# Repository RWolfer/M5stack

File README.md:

# M5stack
M5Stack PCB-Layouts, EAGLE-library and Information

#Board "Atomic":
https://docs.m5stack.com/#/en/atom/atomic
PCB-File: https://github.com/m5stack/M5-3D_and_PCB/blob/master/Atomic_V1.0.PcbDoc

#Board "Atom Hub Proto"
https://docs.m5stack.com/#/en/atom/atomhub
PCB-File: https://github.com/m5stack/m5-structural-design-file/blob/master/PCB/AtomHubProto.PcbDoc

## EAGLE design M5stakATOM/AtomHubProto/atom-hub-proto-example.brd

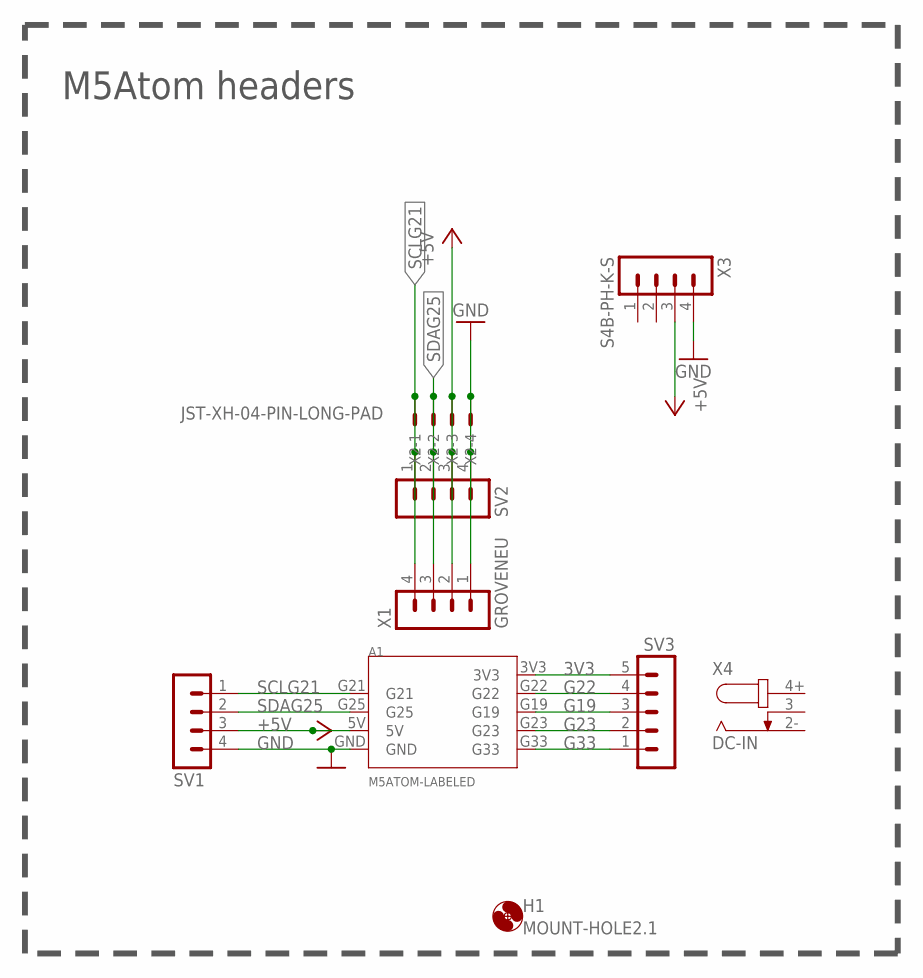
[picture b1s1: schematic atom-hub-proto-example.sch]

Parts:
A1: M5ATOM-LABELED; M5ATOM-W/-LABELS
H1: MOUNT-HOLE2.1; 2,1
SV1, SV2: MA04-1
SV3: MA05-1
X1: GROVENEU; GROVE-NEU
X2: JST-XH-04-PIN-LONG-PAD; JST-XH-04-PACKAGE-LONG-PAD
X3: S4B-PH-K-S
X4: DC-IN; DC-IN-TH_DC-0440-2.5A-2.0

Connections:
3V3: A1.3V3, SV3.5
+5V: A1.5V, SV1.3, SV2.3, X1.2, X2.3, X3.3
G19: A1.G19, SV3.3
G22: A1.G22, SV3.4
G23: A1.G23, SV3.2
G33: A1.G33, SV3.1
GND: A1.GND, SV1.4, SV2.4, X1.1, X2.4, X3.4
SCLG21: A1.G21, SV1.1, SV2.1, X1.4, X2.1
SDAG25: A1.G25, SV1.2, SV2.2, X1.3, X2.2

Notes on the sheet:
M5Atom headers

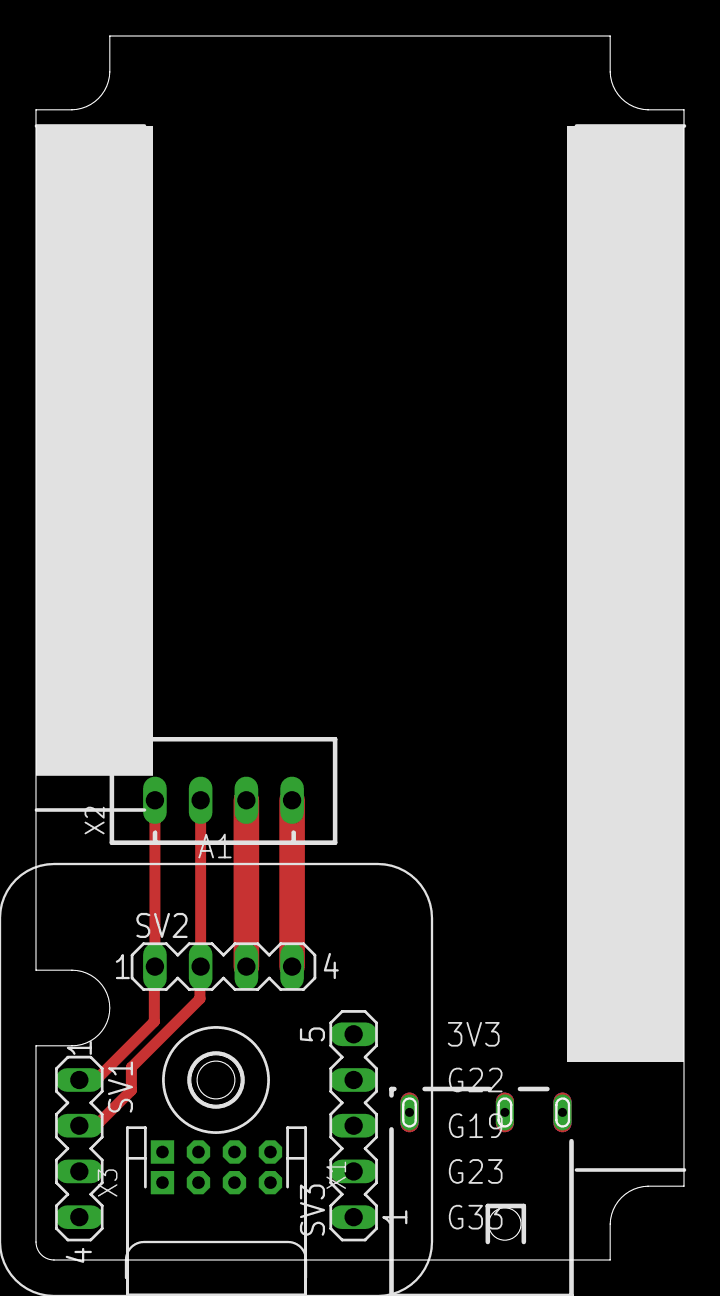
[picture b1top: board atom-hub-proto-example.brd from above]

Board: 2 copper layers, 36.0 x 68.0 mm, 9 parts (0 on the bottom side), 9 nets.

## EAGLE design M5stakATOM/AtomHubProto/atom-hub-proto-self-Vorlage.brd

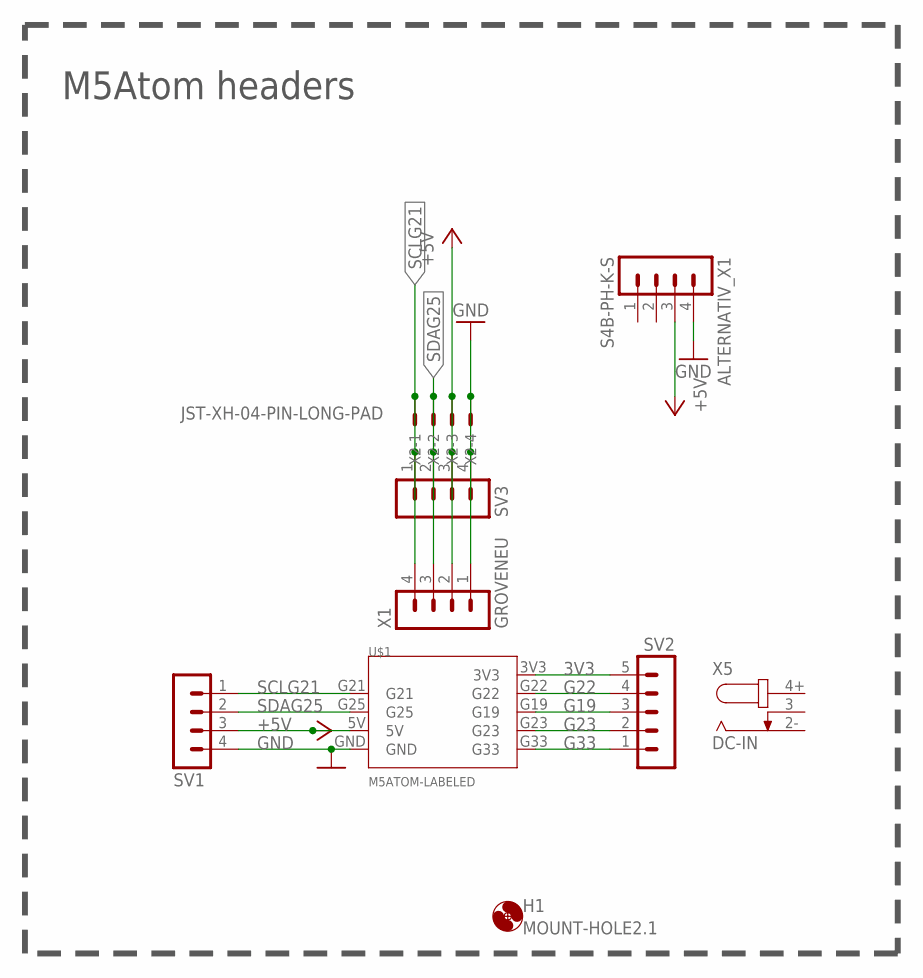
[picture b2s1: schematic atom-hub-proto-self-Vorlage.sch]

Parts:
ALTERNATIV_X1: S4B-PH-K-S
H1: MOUNT-HOLE2.1; 2,1
SV1, SV3: MA04-1
SV2: MA05-1
U$1: M5ATOM-LABELED; M5ATOM-W/-LABELS
X1: GROVENEU; GROVE-NEU
X2: JST-XH-04-PIN-LONG-PAD; JST-XH-04-PACKAGE-LONG-PAD
X5: DC-IN; DC-IN-TH_DC-0440-2.5A-2.0

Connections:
3V3: SV2.5, U$1.3V3
+5V: ALTERNATIV_X1.3, SV1.3, SV3.3, U$1.5V, X1.2, X2.3
G19: SV2.3, U$1.G19
G22: SV2.4, U$1.G22
G23: SV2.2, U$1.G23
G33: SV2.1, U$1.G33
GND: ALTERNATIV_X1.4, SV1.4, SV3.4, U$1.GND, X1.1, X2.4
SCLG21: SV1.1, SV3.1, U$1.G21, X1.4, X2.1
SDAG25: SV1.2, SV3.2, U$1.G25, X1.3, X2.2

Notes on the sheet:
M5Atom headers

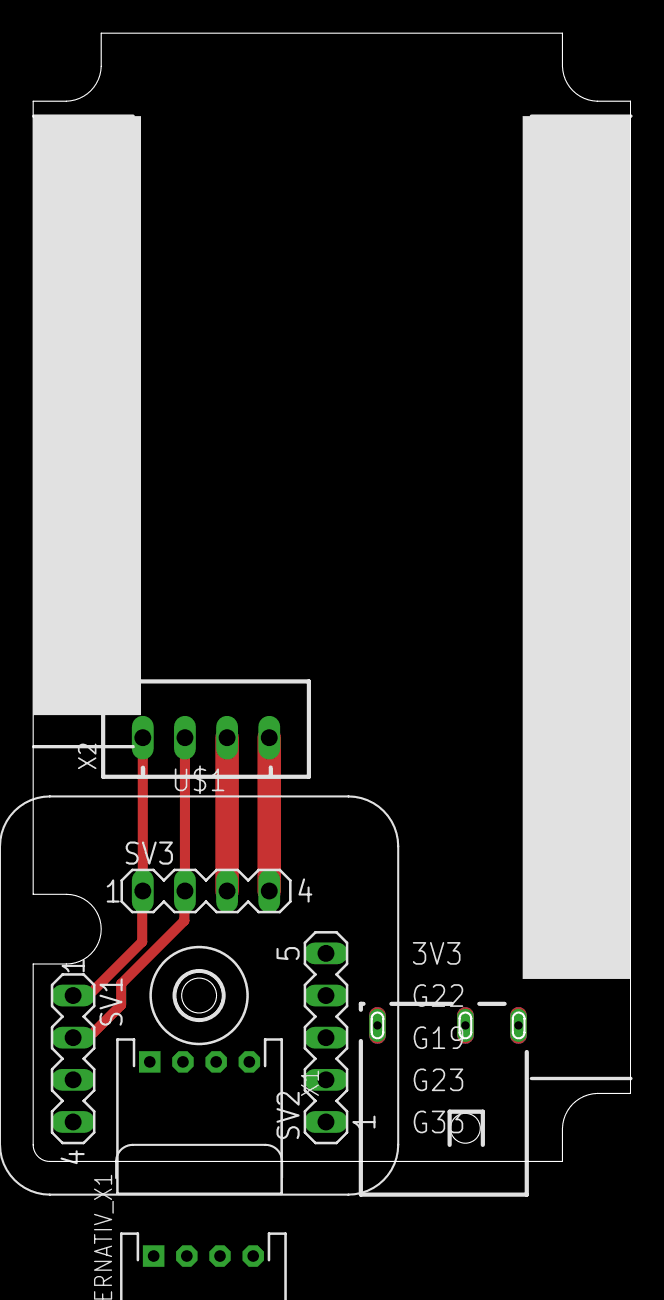
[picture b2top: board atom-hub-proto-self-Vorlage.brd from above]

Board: 2 copper layers, 36.0 x 68.0 mm, 9 parts (0 on the bottom side), 9 nets.

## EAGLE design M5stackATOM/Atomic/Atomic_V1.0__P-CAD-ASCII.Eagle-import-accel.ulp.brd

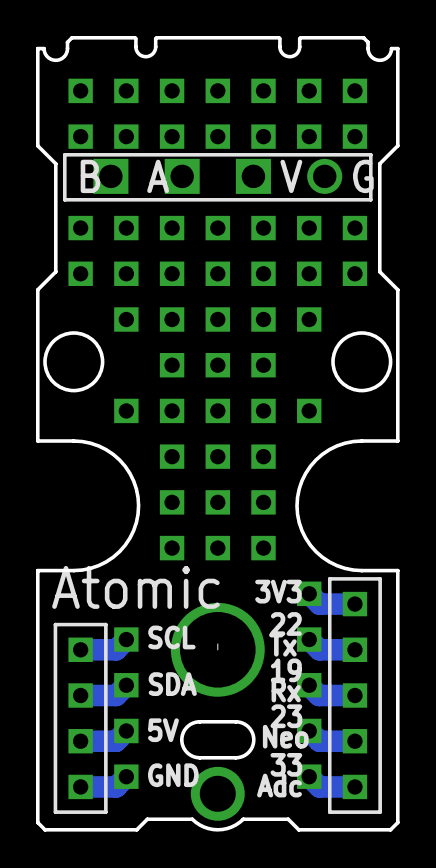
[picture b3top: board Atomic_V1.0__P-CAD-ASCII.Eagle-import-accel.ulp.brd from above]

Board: 2 copper layers, 20.0 x 44.0 mm, 76 parts (0 on the bottom side), 8 nets.

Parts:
DUMMY1: P:EX165Y165D1651
DUMMY2, DUMMY3, DUMMY4, DUMMY5, DUMMY6, DUMMY7, DUMMY8, DUMMY9, DUMMY10, DUMMY21, DUMMY22, DUMMY23, DUMMY24, DUMMY25, DUMMY26, DUMMY27, DUMMY28, DUMMY29, DUMMY30, DUMMY31, DUMMY32, DUMMY33, DUMMY34, DUMMY35, DUMMY36, DUMMY37, DUMMY38, DUMMY39, DUMMY40, DUMMY41, DUMMY42, DUMMY43, DUMMY44, DUMMY45, DUMMY46, DUMMY47, DUMMY48, DUMMY49, DUMMY50, DUMMY51, DUMMY52, DUMMY53, DUMMY54, DUMMY55, DUMMY56, DUMMY57, DUMMY58, DUMMY59, DUMMY60, DUMMY61, DUMMY62, DUMMY63, DUMMY64, DUMMY65, DUMMY66, DUMMY71, DUMMY72, DUMMY73, DUMMY74: P:RRX55Y55D331
DUMMY11: P:EX79Y79D791
DUMMY12, DUMMY13, DUMMY14, DUMMY15, DUMMY16, DUMMY17, DUMMY18, DUMMY20: P:RRX47Y47D331
DUMMY19: P:SX47Y47D331
DUMMY67: P:EX71Y71D511
DUMMY68, DUMMY69: P:RRX71Y71D511
DUMMY70: P:SX71Y71D511
DUMMY75: EF154X154MID1
DUMMY76: EF154X154MID2

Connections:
S$1: DUMMY10.P$1, DUMMY18.P$1
S$2: DUMMY9.P$1, DUMMY17.P$1
S$4: DUMMY5.P$1, DUMMY15.P$1
S$5: DUMMY3.P$1, DUMMY14.P$1
S$6: DUMMY8.P$1, DUMMY12.P$1
S$7: DUMMY6.P$1, DUMMY13.P$1
S$8: DUMMY4.P$1, DUMMY19.P$1
S$9: DUMMY2.P$1, DUMMY20.P$1

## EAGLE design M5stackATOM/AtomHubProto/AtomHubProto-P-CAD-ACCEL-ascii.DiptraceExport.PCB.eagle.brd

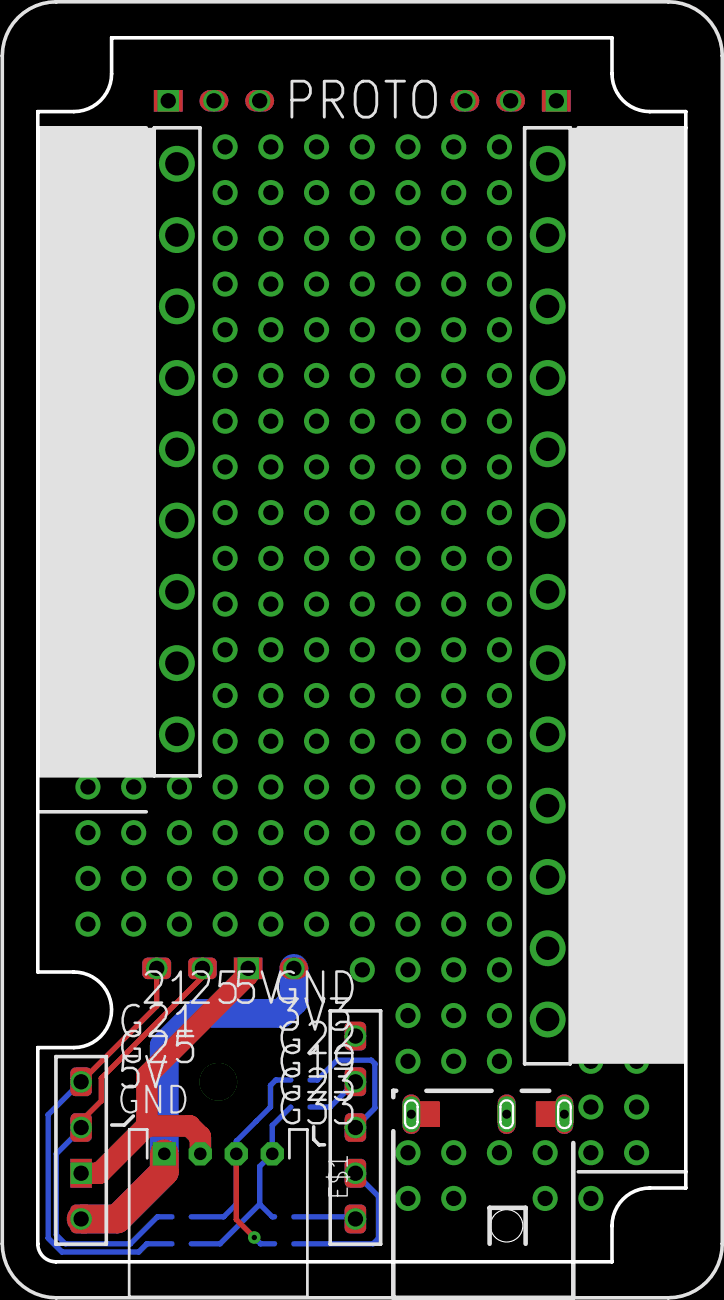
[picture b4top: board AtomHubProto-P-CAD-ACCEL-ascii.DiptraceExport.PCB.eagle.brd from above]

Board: 2 copper layers, 36.0 x 68.0 mm, 304 parts (0 on the bottom side), 4 nets.

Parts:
DC-IN-TH_DC-0440-2.5A-2.0: XKB Connectivity DC-0440-2.5A-2.0; DC-IN-TH_DC-0440-2.5A-2.0
E$1: GROVE-NEU
FREEPAD0, FREEPAD1, FREEPAD2, FREEPAD3, FREEPAD4, FREEPAD5, FREEPAD6, FREEPAD7, FREEPAD8, FREEPAD9, FREEPAD10, FREEPAD11, FREEPAD12, FREEPAD13, FREEPAD14, FREEPAD15, FREEPAD16, FREEPAD17, FREEPAD18, FREEPAD19, FREEPAD20, FREEPAD21, FREEPAD22, FREEPAD23, FREEPAD24, FREEPAD25, FREEPAD26, FREEPAD27, FREEPAD28, FREEPAD29, FREEPAD30, FREEPAD31, FREEPAD32, FREEPAD33, FREEPAD34, FREEPAD35, FREEPAD36, FREEPAD37, FREEPAD38, FREEPAD39, FREEPAD40, FREEPAD41, FREEPAD42, FREEPAD43, FREEPAD44, FREEPAD45, FREEPAD46, FREEPAD47, FREEPAD48, FREEPAD49, FREEPAD50, FREEPAD51, FREEPAD52, FREEPAD53, FREEPAD54, FREEPAD55, FREEPAD56, FREEPAD57, FREEPAD58, FREEPAD59, FREEPAD60, FREEPAD61, FREEPAD62, FREEPAD63, FREEPAD64, FREEPAD65, FREEPAD66, FREEPAD67, FREEPAD68, FREEPAD69, FREEPAD70, FREEPAD71, FREEPAD72, FREEPAD73, FREEPAD74, FREEPAD75, FREEPAD76, FREEPAD77, FREEPAD78, FREEPAD79, FREEPAD80, FREEPAD81, FREEPAD82, FREEPAD83, FREEPAD84, FREEPAD85, FREEPAD86, FREEPAD87, FREEPAD88, FREEPAD89, FREEPAD90, FREEPAD91, FREEPAD92, FREEPAD93, FREEPAD94, FREEPAD95, FREEPAD96, FREEPAD97, FREEPAD98, FREEPAD99, FREEPAD100, FREEPAD101, FREEPAD102, FREEPAD103, FREEPAD104, FREEPAD105, FREEPAD106, FREEPAD107, FREEPAD108, FREEPAD109, FREEPAD110, FREEPAD111, FREEPAD112, FREEPAD113, FREEPAD114, FREEPAD115, FREEPAD116, FREEPAD117, FREEPAD118, FREEPAD119, FREEPAD120, FREEPAD121, FREEPAD122, FREEPAD123, FREEPAD124, FREEPAD125, FREEPAD126, FREEPAD127, FREEPAD128, FREEPAD129, FREEPAD130, FREEPAD131, FREEPAD132, FREEPAD133, FREEPAD134, FREEPAD135, FREEPAD136, FREEPAD137, FREEPAD138, FREEPAD139, FREEPAD140, FREEPAD141, FREEPAD142, FREEPAD143, FREEPAD144, FREEPAD145, FREEPAD146, FREEPAD147, FREEPAD148, FREEPAD149, FREEPAD150, FREEPAD151, FREEPAD152, FREEPAD153, FREEPAD154, FREEPAD155, FREEPAD156, FREEPAD157, FREEPAD158, FREEPAD159, FREEPAD160, FREEPAD161, FREEPAD162, FREEPAD163, FREEPAD164, FREEPAD165, FREEPAD166, FREEPAD167, FREEPAD168, FREEPAD169, FREEPAD170, FREEPAD171, FREEPAD172, FREEPAD173, FREEPAD174, FREEPAD175, FREEPAD176, FREEPAD177, FREEPAD178, FREEPAD179, FREEPAD180, FREEPAD181, FREEPAD182, FREEPAD183, FREEPAD184, FREEPAD185, FREEPAD186, FREEPAD187, FREEPAD188, FREEPAD189, FREEPAD190, FREEPAD191, FREEPAD192, FREEPAD193, FREEPAD194, FREEPAD195, FREEPAD196, FREEPAD197, FREEPAD198, FREEPAD199, FREEPAD200, FREEPAD201, FREEPAD202, FREEPAD203, FREEPAD204, FREEPAD205, FREEPAD206, FREEPAD207, FREEPAD208, FREEPAD209, FREEPAD210, FREEPAD211, FREEPAD212, FREEPAD213, FREEPAD214, FREEPAD215, FREEPAD216, FREEPAD237, FREEPAD238, FREEPAD239, FREEPAD240, FREEPAD241, FREEPAD242, FREEPAD243, FREEPAD244, FREEPAD245, FREEPAD258, FREEPAD269, FREEPAD270, FREEPAD271: FREEPAD
FREEPAD217, FREEPAD218, FREEPAD219, FREEPAD220, FREEPAD221, FREEPAD222, FREEPAD223, FREEPAD225: FREEPAD; FREEPAD_FREEPAD217
FREEPAD224: FREEPAD; FREEPAD_FREEPAD224
FREEPAD226: FREEPAD; FREEPAD_FREEPAD226
FREEPAD227, FREEPAD229, FREEPAD230, FREEPAD232, FREEPAD233: FREEPAD; FREEPAD_FREEPAD227
FREEPAD228, FREEPAD231, FREEPAD234: FREEPAD; FREEPAD_FREEPAD228
FREEPAD235, FREEPAD236: FREEPAD; FREEPAD_FREEPAD235
FREEPAD246, FREEPAD247, FREEPAD248, FREEPAD249, FREEPAD250, FREEPAD251, FREEPAD252, FREEPAD253, FREEPAD254, FREEPAD255, FREEPAD256, FREEPAD257, FREEPAD259, FREEPAD260, FREEPAD261, FREEPAD262, FREEPAD263, FREEPAD264, FREEPAD265, FREEPAD266, FREEPAD267, FREEPAD268: FREEPAD; FREEPAD_FREEPAD246
FREEPAD272, FREEPAD273: FREEPAD; FREEPAD_FREEPAD272
FREEPAD274, FREEPAD275, FREEPAD276, FREEPAD277: FREEPAD; FREEPAD_FREEPAD274
FREEPAD278, FREEPAD281, FREEPAD282, FREEPAD285, FREEPAD286, FREEPAD289, FREEPAD290, FREEPAD293, FREEPAD294, FREEPAD297, FREEPAD298, FREEPAD301: FREEPAD; FREEPAD_FREEPAD278
FREEPAD279, FREEPAD280, FREEPAD283, FREEPAD284, FREEPAD287, FREEPAD288, FREEPAD291, FREEPAD292, FREEPAD295, FREEPAD296, FREEPAD299, FREEPAD300: FREEPAD; FREEPAD_FREEPAD279

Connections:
5V: FREEPAD224.1, FREEPAD234.1
GND: FREEPAD225.1, FREEPAD233.1, FREEPAD274.1, FREEPAD277.1
SCL: FREEPAD217.1, FREEPAD236.1, FREEPAD284.1, FREEPAD285.1
SDA: FREEPAD218.1, FREEPAD235.1, FREEPAD278.1, FREEPAD279.1

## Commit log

2021-03-18 add ATOMIC proto-board Altium PcbDoc
2021-03-18 Add exports and screenshot
2021-03-18 Add Eagle import version (import-ACCEL.ulp), moved to 0.1mm grid
2021-03-18 small improvements
2021-03-18 Add M5stakATOM/AtomHubProto...
2021-03-31 add common.lbr used in AtomHubProto-P-CAD-ACCEL-ascii.DiptraceExport.PCB.eagle.brd
2021-04-01 Boarposition in altium um 0.027mm verschoben... Jetzt in Eagle richtig. DC-plug ergänzt
2021-04-01 Groveneu mit Symbol hinzugefügt
2021-04-01 add template: atom-hub-proto-self-Vorlage.xxx
2021-04-01 changed and added some lines (enclosure)
2021-04-02 add script AtomHubProto/atom-hub-proto-self-template-board-outline.scr
2021-04-06 add position (vias) to outline template script
2021-04-06 add atom-hub-proto-self-template-board-outline.xxx update script
2021-04-08 add gap in enclosure outline
2021-04-16 add original M5stackAtom-proto-hub.png PCB-picture
2021-04-16 add example: atom-hub-proto-example.xxx
2021-04-16 rename main folder M5stackATOM
